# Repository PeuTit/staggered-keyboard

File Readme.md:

# Custom staggered keyboard for Prototyping project

This repository holds the files related to the design of the pcb for my school project, a custom keyboard.

!Insert photo of the finished keyboard here!

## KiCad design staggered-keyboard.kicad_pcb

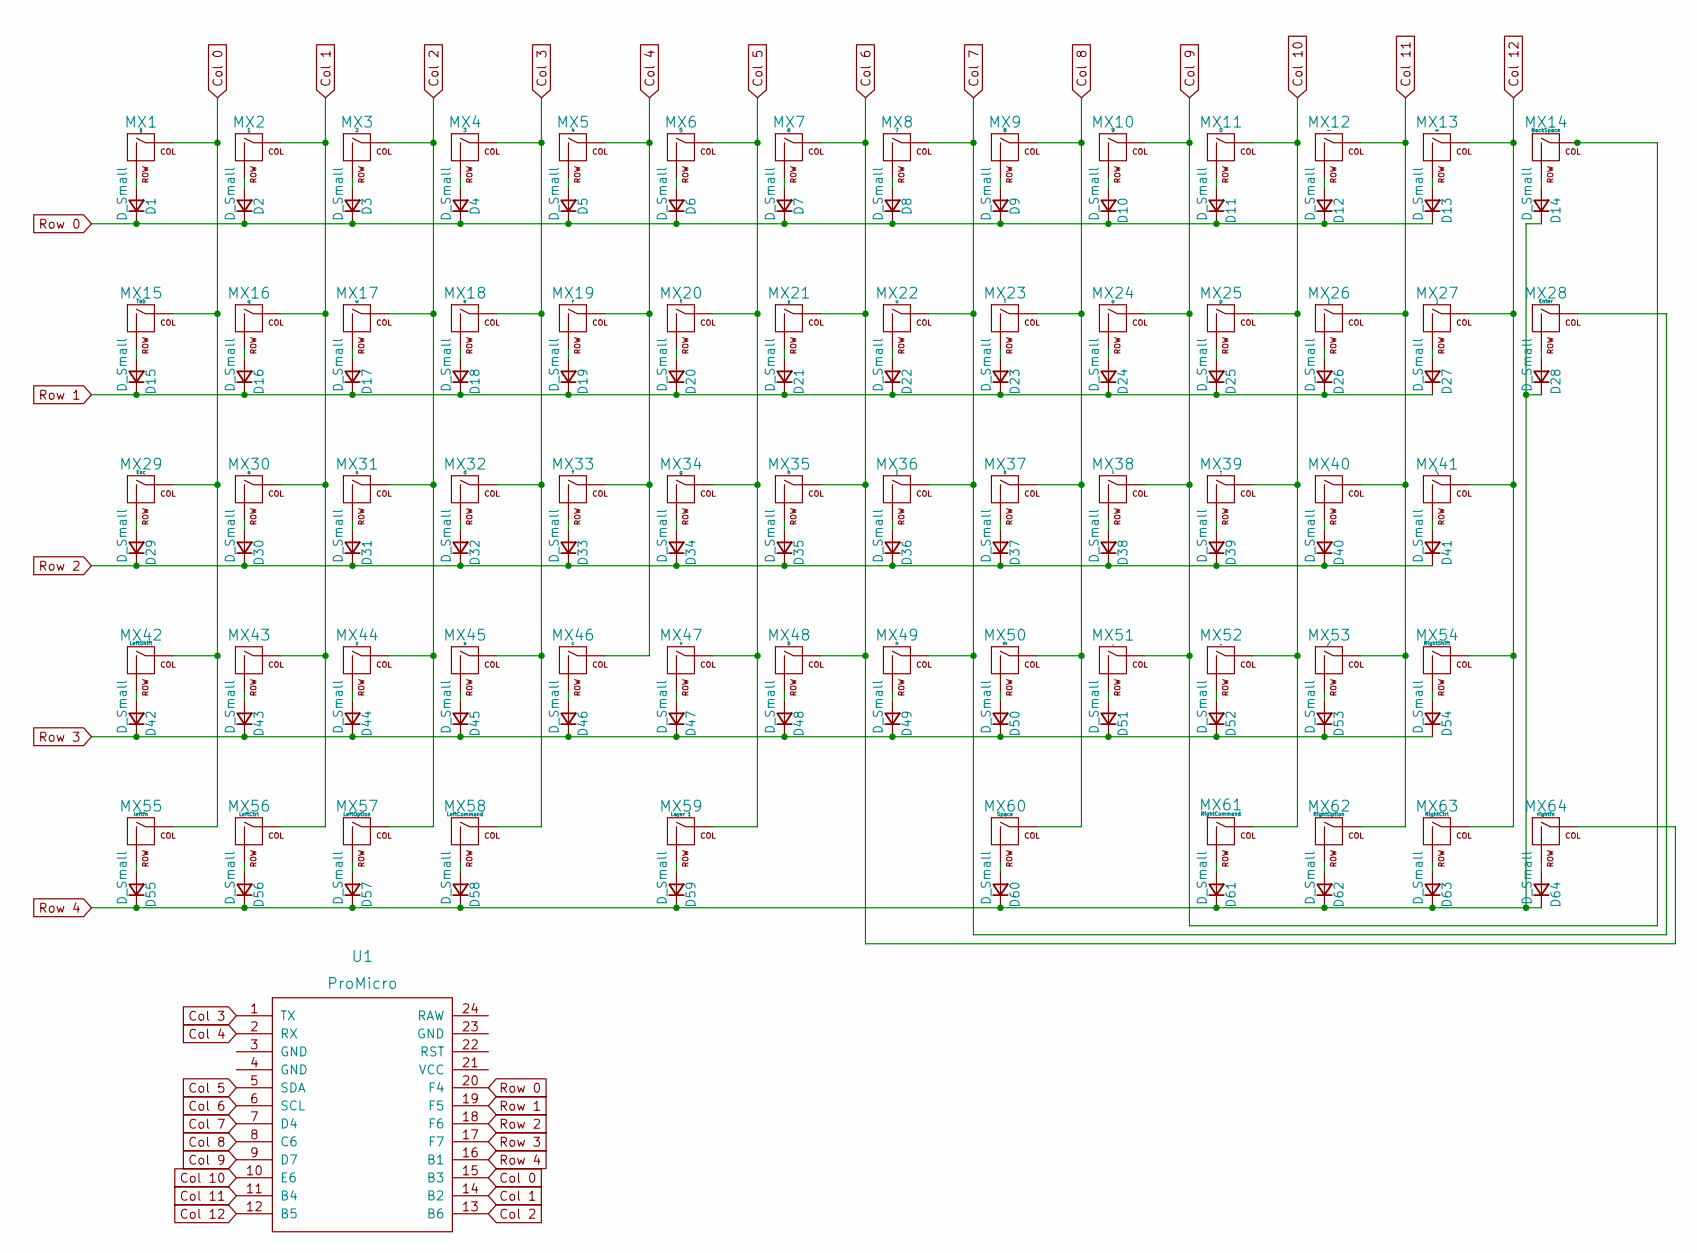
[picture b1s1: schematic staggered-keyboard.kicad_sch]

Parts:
D1, D2, D3, D4, D5, D6, D7, D8, D9, D10, D11, D12, D13, D14, D15, D16, D17, D18, D19, D20, D21, D22, D23, D24, D25, D26, D27, D28, D29, D30, D31, D32, D33, D34, D35, D36, D37, D38, D39, D40, D41, D42, D43, D44, D45, D46, D47, D48, D49, D50, D51, D52, D53, D54, D55, D56, D57, D58, D59, D60, D61, D62, D63, D64: D_Small; D_SOD-123
MX1: §; MXOnly-1U-NoLED
MX2: 1; MXOnly-1U-NoLED
MX3: 2; MXOnly-1U-NoLED
MX4: 3; MXOnly-1U-NoLED
MX5: 4; MXOnly-1U-NoLED
MX6: 5; MXOnly-1U-NoLED
MX7: 6; MXOnly-1U-NoLED
MX8: 7; MXOnly-1U-NoLED
MX9: 8; MXOnly-1U-NoLED
MX10: 9; MXOnly-1U-NoLED
MX11: 0; MXOnly-1U-NoLED
MX12: -; MXOnly-1U-NoLED
MX13: =; MXOnly-1U-NoLED
MX14: BackSpace; MXOnly-2U-NoLED
MX15: Tab; MXOnly-1.5U-NoLED
MX16: q; MXOnly-1U-NoLED
MX17: w; MXOnly-1U-NoLED
MX18: e; MXOnly-1U-NoLED
MX19: r; MXOnly-1U-NoLED
MX20: t; MXOnly-1U-NoLED
MX21: y; MXOnly-1U-NoLED
MX22: u; MXOnly-1U-NoLED
MX23: i; MXOnly-1U-NoLED
MX24: o; MXOnly-1U-NoLED
MX25: p; MXOnly-1U-NoLED
MX26: [; MXOnly-1U-NoLED
MX27: ]; MXOnly-1U-NoLED
MX28: Enter; MXOnly-ISO-NoLED
MX29: Esc; MXOnly-1.75U-NoLED
MX30: a; MXOnly-1U-NoLED
MX31: s; MXOnly-1U-NoLED
MX32: d; MXOnly-1U-NoLED
MX33: f; MXOnly-1U-NoLED
MX34: g; MXOnly-1U-NoLED
MX35: h; MXOnly-1U-NoLED
MX36: j; MXOnly-1U-NoLED
MX37: k; MXOnly-1U-NoLED
MX38: l; MXOnly-1U-NoLED
MX39: ;; MXOnly-1U-NoLED
MX40: '; MXOnly-1U-NoLED
MX41: \; MXOnly-1U-NoLED
MX42: LeftShift; MXOnly-1.25U-NoLED
MX43: `; MXOnly-1U-NoLED
MX44: z; MXOnly-1U-NoLED
MX45: x; MXOnly-1U-NoLED
MX46: c; MXOnly-1U-NoLED
MX47: v; MXOnly-1U-NoLED
MX48: b; MXOnly-1U-NoLED
MX49: n; MXOnly-1U-NoLED
MX50: m; MXOnly-1U-NoLED
MX51: ,; MXOnly-1U-NoLED
MX52: .; MXOnly-1U-NoLED
MX53: /; MXOnly-1U-NoLED
MX54: RightShift; MXOnly-2.75U-NoLED
MX55: leftfn; MXOnly-1U-NoLED
MX56: LeftCtrl; MXOnly-1.25U-NoLED
MX57: LeftOption; MXOnly-1.25U-NoLED
MX58: LeftCommand; MXOnly-1.25U-NoLED
MX59: Layer 1; MXOnly-2.75U-NoLED
MX60: Space; MXOnly-2.75U-NoLED
MX61: RightCommand; MXOnly-1.25U-NoLED
MX62: RightOption; MXOnly-1.25U-NoLED
MX63: RightCtrl; MXOnly-1.25U-NoLED
MX64: rightfn; MXOnly-1U-NoLED
U1: ProMicro

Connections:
Col 0: MX1.1 (COL), MX15.1 (COL), MX29.1 (COL), MX42.1 (COL), MX55.1 (COL), U1.15 (B3)
Col 1: MX2.1 (COL), MX16.1 (COL), MX30.1 (COL), MX43.1 (COL), MX56.1 (COL), U1.14 (B2)
Col 2: MX3.1 (COL), MX17.1 (COL), MX31.1 (COL), MX44.1 (COL), MX57.1 (COL), U1.13 (B6)
Col 3: MX4.1 (COL), MX18.1 (COL), MX32.1 (COL), MX45.1 (COL), MX58.1 (COL), U1.1 (TX)
Col 4: MX5.1 (COL), MX19.1 (COL), MX33.1 (COL), MX46.1 (COL), U1.2 (RX)
Col 5: MX6.1 (COL), MX20.1 (COL), MX34.1 (COL), MX47.1 (COL), MX59.1 (COL), U1.5 (SDA)
Col 6: MX7.1 (COL), MX21.1 (COL), MX35.1 (COL), MX48.1 (COL), MX64.1 (COL), U1.6 (SCL)
Col 7: MX8.1 (COL), MX22.1 (COL), MX28.1 (COL), MX36.1 (COL), MX49.1 (COL), U1.7 (D4)
Col 8: MX9.1 (COL), MX23.1 (COL), MX37.1 (COL), MX50.1 (COL), MX60.1 (COL), U1.8 (C6)
Col 9: MX10.1 (COL), MX14.1 (COL), MX24.1 (COL), MX38.1 (COL), MX51.1 (COL), U1.9 (D7)
Col 10: MX11.1 (COL), MX25.1 (COL), MX39.1 (COL), MX52.1 (COL), MX61.1 (COL), U1.10 (E6)
Col 11: MX12.1 (COL), MX26.1 (COL), MX40.1 (COL), MX53.1 (COL), MX62.1 (COL), U1.11 (B4)
Col 12: MX13.1 (COL), MX27.1 (COL), MX41.1 (COL), MX54.1 (COL), MX63.1 (COL), U1.12 (B5)
unnamed: D1.2 (A), MX1.2 (ROW)
unnamed: D2.2 (A), MX2.2 (ROW)
unnamed: D3.2 (A), MX3.2 (ROW)
unnamed: D4.2 (A), MX4.2 (ROW)
unnamed: D5.2 (A), MX5.2 (ROW)
unnamed: D6.2 (A), MX6.2 (ROW)
unnamed: D7.2 (A), MX7.2 (ROW)
unnamed: D8.2 (A), MX8.2 (ROW)
unnamed: D9.2 (A), MX9.2 (ROW)
unnamed: D10.2 (A), MX10.2 (ROW)
unnamed: D11.2 (A), MX11.2 (ROW)
unnamed: D12.2 (A), MX12.2 (ROW)
unnamed: D13.2 (A), MX13.2 (ROW)
unnamed: D14.2 (A), MX14.2 (ROW)
unnamed: D15.2 (A), MX15.2 (ROW)
unnamed: D16.2 (A), MX16.2 (ROW)
unnamed: D17.2 (A), MX17.2 (ROW)
unnamed: D18.2 (A), MX18.2 (ROW)
unnamed: D19.2 (A), MX19.2 (ROW)
unnamed: D20.2 (A), MX20.2 (ROW)
unnamed: D21.2 (A), MX21.2 (ROW)
unnamed: D22.2 (A), MX22.2 (ROW)
unnamed: D23.2 (A), MX23.2 (ROW)
unnamed: D24.2 (A), MX24.2 (ROW)
unnamed: D25.2 (A), MX25.2 (ROW)
unnamed: D26.2 (A), MX26.2 (ROW)
unnamed: D27.2 (A), MX27.2 (ROW)
unnamed: D28.2 (A), MX28.2 (ROW)
unnamed: D29.2 (A), MX29.2 (ROW)
unnamed: D30.2 (A), MX30.2 (ROW)
unnamed: D31.2 (A), MX31.2 (ROW)
unnamed: D32.2 (A), MX32.2 (ROW)
unnamed: D33.2 (A), MX33.2 (ROW)
unnamed: D34.2 (A), MX34.2 (ROW)
unnamed: D35.2 (A), MX35.2 (ROW)
unnamed: D36.2 (A), MX36.2 (ROW)
unnamed: D37.2 (A), MX37.2 (ROW)
unnamed: D38.2 (A), MX38.2 (ROW)
unnamed: D39.2 (A), MX39.2 (ROW)
unnamed: D40.2 (A), MX40.2 (ROW)
unnamed: D41.2 (A), MX41.2 (ROW)
unnamed: D42.2 (A), MX42.2 (ROW)
unnamed: D43.2 (A), MX43.2 (ROW)
unnamed: D44.2 (A), MX44.2 (ROW)
unnamed: D45.2 (A), MX45.2 (ROW)
unnamed: D46.2 (A), MX46.2 (ROW)
unnamed: D47.2 (A), MX47.2 (ROW)
unnamed: D48.2 (A), MX48.2 (ROW)
unnamed: D49.2 (A), MX49.2 (ROW)
unnamed: D50.2 (A), MX50.2 (ROW)
unnamed: D51.2 (A), MX51.2 (ROW)
unnamed: D52.2 (A), MX52.2 (ROW)
unnamed: D53.2 (A), MX53.2 (ROW)
unnamed: D54.2 (A), MX54.2 (ROW)
unnamed: D55.2 (A), MX55.2 (ROW)
unnamed: D56.2 (A), MX56.2 (ROW)
unnamed: D57.2 (A), MX57.2 (ROW)
unnamed: D58.2 (A), MX58.2 (ROW)
unnamed: D59.2 (A), MX59.2 (ROW)
unnamed: D60.2 (A), MX60.2 (ROW)
unnamed: D61.2 (A), MX61.2 (ROW)
unnamed: D62.2 (A), MX62.2 (ROW)
unnamed: D63.2 (A), MX63.2 (ROW)
unnamed: D64.2 (A), MX64.2 (ROW)
Row 0: D1.1 (K), D2.1 (K), D3.1 (K), D4.1 (K), D5.1 (K), D6.1 (K), D7.1 (K), D8.1 (K), D9.1 (K), D10.1 (K), D11.1 (K), D12.1 (K), D13.1 (K), U1.20 (F4)
Row 1: D15.1 (K), D16.1 (K), D17.1 (K), D18.1 (K), D19.1 (K), D20.1 (K), D21.1 (K), D22.1 (K), D23.1 (K), D24.1 (K), D25.1 (K), D26.1 (K), D27.1 (K), U1.19 (F5)
Row 2: D29.1 (K), D30.1 (K), D31.1 (K), D32.1 (K), D33.1 (K), D34.1 (K), D35.1 (K), D36.1 (K), D37.1 (K), D38.1 (K), D39.1 (K), D40.1 (K), D41.1 (K), U1.18 (F6)
Row 3: D42.1 (K), D43.1 (K), D44.1 (K), D45.1 (K), D46.1 (K), D47.1 (K), D48.1 (K), D49.1 (K), D50.1 (K), D51.1 (K), D52.1 (K), D53.1 (K), D54.1 (K), U1.17 (F7)
Row 4: D14.1 (K), D28.1 (K), D55.1 (K), D56.1 (K), D57.1 (K), D58.1 (K), D59.1 (K), D60.1 (K), D61.1 (K), D62.1 (K), D63.1 (K), D64.1 (K), U1.16 (B1)

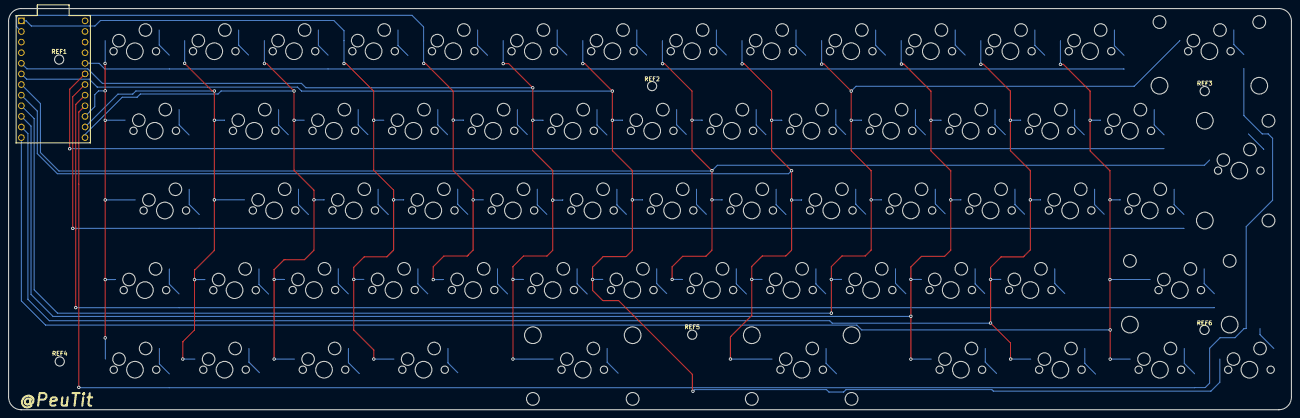
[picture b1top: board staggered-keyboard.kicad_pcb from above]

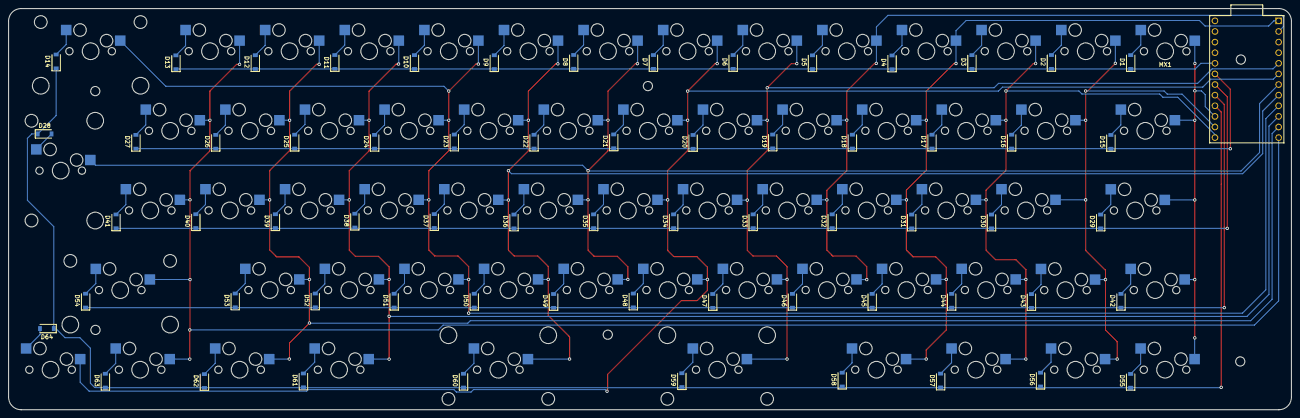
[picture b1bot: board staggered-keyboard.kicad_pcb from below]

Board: 2 copper layers, 307.0 x 96.0 mm, 135 parts (64 on the bottom side), 82 nets.

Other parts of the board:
REF1, REF2, REF3, REF4, REF5, REF6: MountingHole_2.2mm_M2

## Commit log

2022-09-28 Initialise KiCad project
2022-09-28 Add KiCad Library
2022-09-28 Update .gitignore with auto saved files
2022-09-28 Create key layout
2022-09-28 Place switches on pcb & fix footprint on schematic
2022-09-28 Move diode in place
2022-09-28 Update footprint for 1U switches & align diode for first row
2022-09-28 Finish placing componants & Finish routing switches
2022-09-29 Clean up routing for rows
2022-09-29 Finish routing of the pcb & update layout in schematic
2022-09-29 Fix errors after running DRC
2022-09-30 Update pcb design && various changes
    - Generate Gerber file for production
    - Generate .step file for 3D design
2022-10-01 Add hotswap socket to pcb
2022-10-02 Generate new gerber file
2022-10-02 Clean up routing
2022-10-02 Add new pcb screenshot & create assets folder
2022-10-03 Validate file for production
    Generate BOM & CPL
    Order placed at JLCPCB
2022-10-05 Update fp
2022-10-05 Add readme
